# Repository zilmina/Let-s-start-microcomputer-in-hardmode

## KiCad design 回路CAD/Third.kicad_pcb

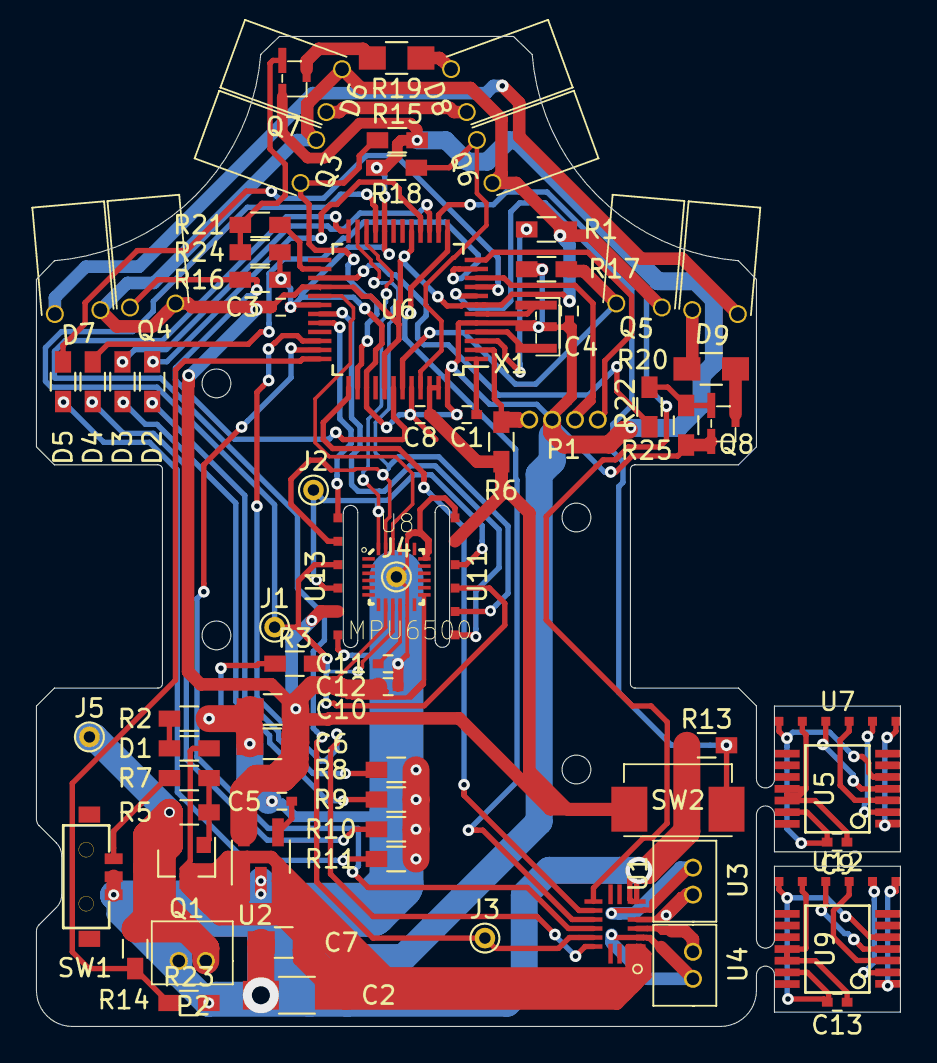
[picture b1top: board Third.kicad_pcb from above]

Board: 2 copper layers, 48.0 x 55.0 mm, 74 parts (0 on the bottom side), 68 nets.

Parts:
C1, C3, C4, C5, C8, C9, C11, C12, C13: 0.1uF; C_0402
C2: 47uF TAJA476K006R; C_1206_HandSoldering
C6, C7: 2.2uF; C_0805_HandSoldering
C10: 10nF; C_0805_HandSoldering
D1: OSTG1608C1A; L_0603_HandSoldering
D2: OSHR1608; L_0603_HandSoldering
D3: OSYL1608; L_0603_HandSoldering
D4: OSBL1608; L_0603_HandSoldering
D5: OSOR1608C1A; L_0603_HandSoldering
D6, D7, D8, D9: OSI5FU3A11C
J1, J2, J3, J4, J5: CONN_01X01_FEMALE; PINTST
P1: ZH_4pin; Half_pitch_4pin
P2: ZH_2pin
Q1: IRLML6402; SOT-23
Q3, Q4, Q5, Q6: LTR-4206E; OSI5FU3A11C
Q7, Q8: PJE260N02; SOT-523
R1, R2, R3, R7, R8, R9, R10, R11, R13, R21, R22: 1kΩ; R_0603_HandSoldering
R5, R24, R25: 100kΩ; R_0603_HandSoldering
R6: 1KΩ; R_0603_HandSoldering
R14, R23: 10kΩ; R_0603_HandSoldering
R15, R16, R17, R18: 300Ω; R_0603_HandSoldering
R19, R20: 4.5Ω; R_0805_HandSoldering
SW1: SSAJ110100
SW2: SW_PUSH; 434123043816
U1: DRV8836; WSON(12)
U2: MIC5323; SOT-23-5_HandSoldering
U3, U4: MOTOR; ZH_2pin
U5, U9: AS5047D; SSOP-14
U6: R5F5631NDDFL; LQFP-48_7x7mm_Pitch0.5mm
U7, U12: male_6pin_plate; male_6pin_plate2plate
U8: MPU6500; QFN40P300X300X105-25N
U11, U13: female_6pin_plate; female_6pin_plate2plate
X1: CSTCE10M0G52-R0

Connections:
/AOUT1: U1.2, U4.2
/AOUT2: U1.3, U4.1
/BOUT1: U1.4, U3.2
/BOUT2: U1.5, U3.1
AD_BATTERY: R14.2, R23.1, U6.36
AENBL: U1.9, U6.13
APHASE: U1.10, U6.35
BATTERY_+: J5.1, P2.1, Q1.2, R5.1, R14.1
BENBL: U1.7, U6.14
BPHASE: U1.8, U6.37
CLK: U6.23, U8.23, U11.2, U13.2
CLK_L_m: U9.2, U12.2
CLK_R_m: U5.2, U7.2
CS_ENCODER_L: U6.32, U13.1
CS_ENCODER_L_m: U9.1, U12.1
CS_ENCODER_R: U6.31, U11.1
CS_ENCODER_R_m: U5.1, U7.1
CS_GYRO: U6.29, U8.22
GND: C1.2, C2.2, C3.2, C4.1, C5.2, C6.2, C7.2, C8.1, C10.2, C11.2, C12.2, J4.1, P1.3, P2.2, Q7.2, Q8.2, R2.2, R3.2, R8.2, R9.2, R10.2, R11.2, R13.1, R15.2, R16.2, R17.2, R18.2, R23.2, R24.2, R25.2, SW1.2, SW1.3, U1.6, U2.2, U6.5, U6.20, U6.30, U6.39, U6.44, U6.48, U8.11, U8.18, U8.20, U11.6, U13.6, X1.2
GND_L_m: C13.2, U9.5, U9.13, U12.6
GND_R_m: C9.2, U5.5, U5.13, U7.6
LED_FRONT: R22.1, U6.27
LED_LF: D3.2, U6.15
LED_LS: D2.2, U6.16
LED_RF: D4.2, U6.11
LED_RS: D5.2, U6.9
LED_SIDE: R21.1, U6.26
MD_MODE: J3.1, U1.11, U6.24
MISO: J1.1, R3.1, U6.21, U8.9, U11.3, U13.3
MISO_L_m: U9.3, U12.3
MISO_R_m: U5.3, U7.3
MOSI: J2.1, U6.22, U8.24, U11.4, U13.4
MOSI_L_m: U9.4, U12.4
MOSI_R_m: U5.4, U7.4
unnamed: C1.1, U6.1
unnamed: C5.1, U2.4
unnamed: C11.1, U8.10
unnamed: D1.1, R2.1
unnamed: D2.1, R8.1
unnamed: D3.1, R9.1
unnamed: D4.1, R10.1
unnamed: D5.1, R11.1
unnamed: D6.1, D8.2
unnamed: D7.1, D9.2
unnamed: D8.1, R19.1
unnamed: D9.1, R20.1
unnamed: Q1.1, R5.2, R7.2
unnamed: Q7.1, R21.2, R24.1
unnamed: Q7.3, R19.2
unnamed: Q8.1, R22.2, R25.1
unnamed: Q8.3, R20.2
unnamed: R1.2, U6.3
unnamed: R7.1, SW1.1
unnamed: U6.4, X1.1
unnamed: U6.6, X1.3
PHOTO_LF: Q4.1, R16.1, U6.42
PHOTO_LS: Q3.1, R15.1, U6.38
PHOTO_RF: Q5.1, R17.1, U6.43
PHOTO_RS: Q6.1, R18.1, U6.45
RXD1: P1.2, U6.10
RX_MODE: P1.4, R6.1, U6.2
SW_1: R13.2, SW2.2, U6.8
TXD1: P1.1, U6.12
VIN: C2.1, C7.1, D1.2, Q1.3, U1.1, U2.1, U2.3
VOUT: C3.1, C4.2, C6.1, C8.2, C10.1, C12.1, D6.2, D7.2, Q3.2, Q4.2, Q5.2, Q6.2, R1.1, R6.2, SW2.1, U2.5, U6.7, U6.17, U6.28, U6.41, U6.46, U6.47, U8.8, U8.13, U11.5, U13.5
VOUT_L_m: C13.1, U9.11, U9.12, U12.5
VOUT_R_m: C9.1, U5.11, U5.12, U7.5
nSLEEP: U1.12, U6.34

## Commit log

2019-03-26 「はじめに」を執筆開始
2019-03-26 目次を追加
2022-04-09 [update]
